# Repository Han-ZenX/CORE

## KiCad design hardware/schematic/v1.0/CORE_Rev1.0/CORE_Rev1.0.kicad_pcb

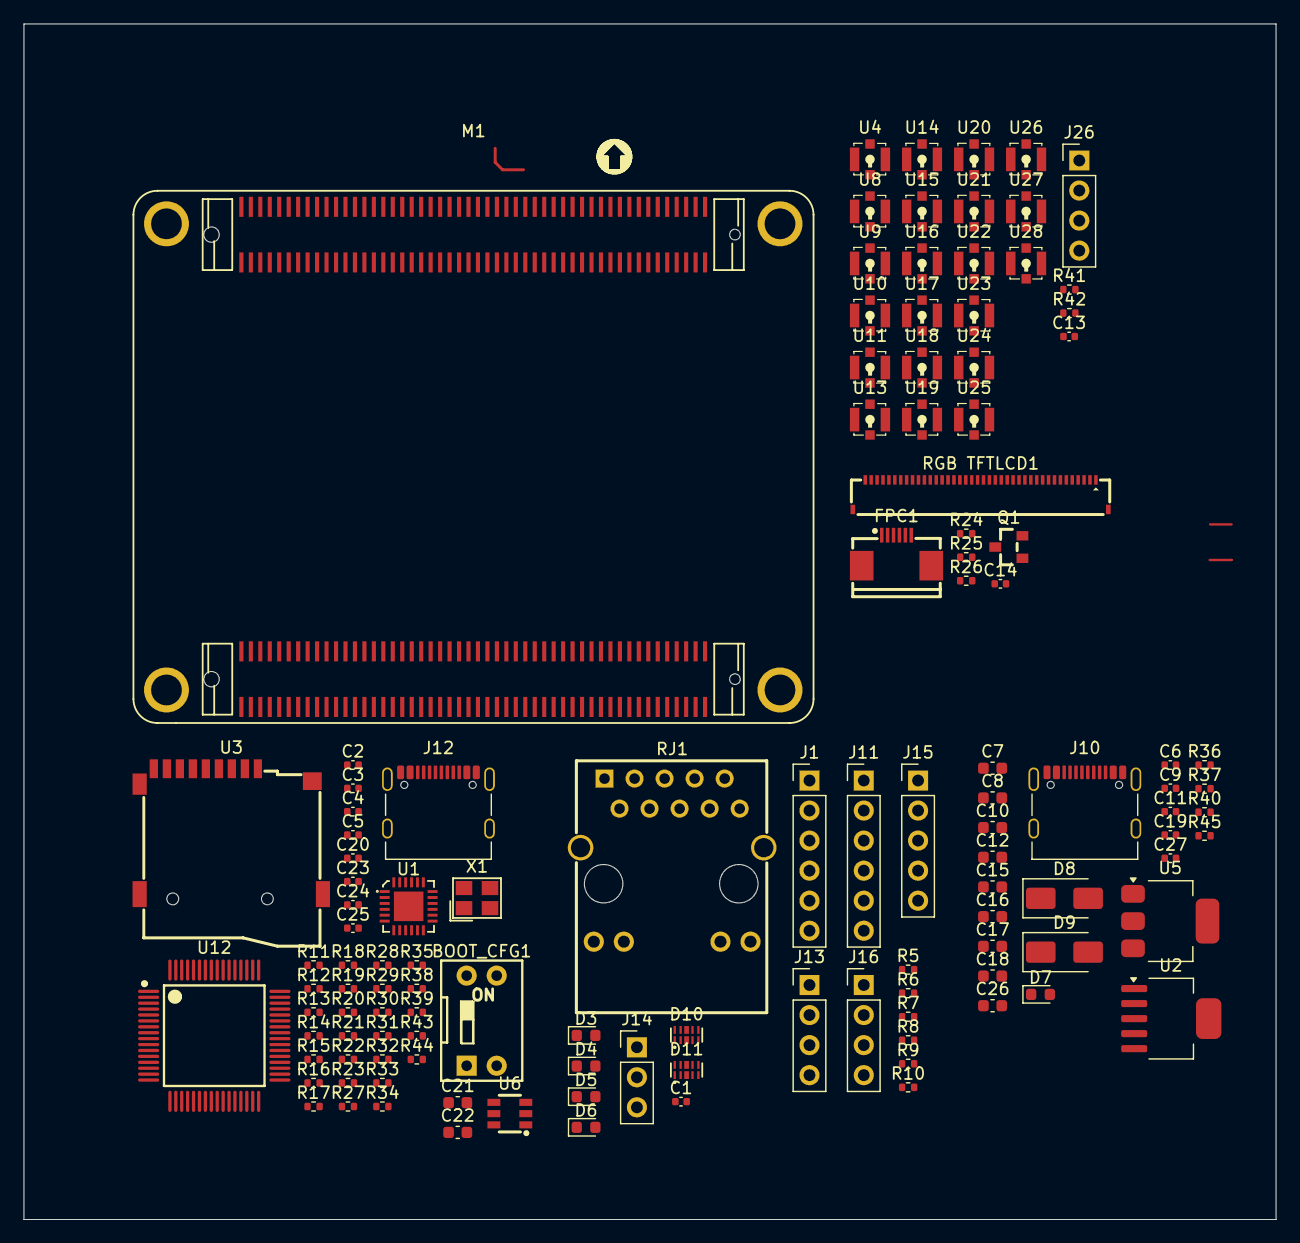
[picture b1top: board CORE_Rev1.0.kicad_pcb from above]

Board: 4 copper layers, 105.9 x 101.1 mm, 120 parts (0 on the bottom side), 163 nets.

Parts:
BOOT_CFG1: CSW-2P; CSW DIP-2P
C1, C2, C3, C5, C6, C11, C14, C19, C20, C23, C27: 100nF; C_0402_1005Metric
C4: 10uF; C_0402_1005Metric
C7, C8, C10, C12, C15, C17, C21, C22, C26: 10uF; C_0603_1608Metric
C9: 10nF; C_0402_1005Metric
C13: 1nF; C_0402_1005Metric
C16, C18: 100nF; C_0603_1608Metric
C24, C25: 30pF; C_0402_1005Metric
D3, D4, D5, D6, D7: LED; LED_0603_1608Metric
D8, D9: SS34; D_SMA
D10, D11: AZ1143-04F_R7G
FPC1: FPC-05F-6PH20
J1, J11: Conn_01x06_Socket; PinHeader_1x06_P2.54mm_Vertical
J10, J12: USB_C_Receptacle_USB2.0_16P; USB_C_Receptacle_Palconn_UTC16-G
J13, J16, J26: Conn_01x04_Socket; PinHeader_1x04_P2.54mm_Vertical
J14: Conn_01x03_Socket; PinHeader_1x03_P2.54mm_Vertical
J15: Conn_01x05_Socket; PinHeader_1x05_P2.54mm_Vertical
M1: ZYNQ7010&7020; ZYNQ7010&7020_CB
Q1: Si2302CDS-T1-GE3
R5, R6, R7, R8, R9, R10: 499R; R_0402_1005Metric
R11, R12: 20K; R_0402_1005Metric
R13, R14, R18, R24, R34: 10K; R_0402_1005Metric
R15, R19, R20, R21, R22, R23: 4.7K; R_0402_1005Metric
R16: 330; R_0402_1005Metric
R17, R40, R43, R44: 0; R_0402_1005Metric
R25, R45: 1K; R_0402_1005Metric
R26: 10; R_0402_1005Metric
R27, R28: 10R; R_0402_1005Metric
R29, R30, R31, R32: 33R; R_0402_1005Metric
R33: 2K; R_0402_1005Metric
R35: 12K/%1; R_0402_1005Metric
R36, R37, R38, R39: 5.1K; R_0402_1005Metric
R41, R42: 49.9; R_0402_1005Metric
RGB TFTLCD1: RGBLCD; LAIL-FPC-CDX01-40P0_5-GW
RJ1: HR911131A
U1: TXS02612RTWR
U2: TPS78633; SOT-223-6
U3: SD_Card; XDFP-0090-012
U4, U8, U9, U10, U11, U13, U14, U15, U16, U17, U18, U19, U20, U21, U22, U23, U24, U25, U26, U27, U28: IPEX1; JLC_IPEX-1
U5: AMS1117-1.8; SOT-223-3_TabPin2
U6: 93LC56BT-I_OT
U12: FT2232HL
X1: X322512MSB4SI

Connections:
+1.8V: C3.2, C17.1, C18.1, U1.5 (VCCA), U5.2 (VO)
+3.3V: C2.2, C4.1, C5.1, C10.2, C14.2, C15.1, C16.1, C19.2, FPC1.2, J1.3, J1.4, J11.3, J11.4, J26.1, R9.1, R10.2, R13.2, R14.2, R18.1, R19.1, R20.1, R21.1, R22.1, R23.1, R34.2, RGB TFTLCD1.1, RGB TFTLCD1.4, U1.17 (VCCB1), U1.21 (VCCB0), U2.4 (OUT), U3.4 (VDD), U5.3 (VI), U6.6 (VCC), U12.4 (VPHY), U12.9 (VPLL), U12.12 (VCORE), U12.20 (VCCIO), U12.31 (VCCIO), U12.37 (VCORE), U12.42 (VCCIO), U12.49 (VREGOUT), U12.50 (VREGIN), U12.56 (VCCIO), U12.64 (VCORE)
+5V: J1.1, J1.2, J11.1, J11.2, M1.J1_1 (1), M1.J1_2 (2), M1.J1_3 (3), M1.J1_4 (4), M1.J1_5 (5), M1.J1_6 (6), M1.J1_7 (7), M1.J1_8 (8), R40.2, R45.1, U2.2 (IN)
+5V_IN: C26.1, C27.1, D9.2 (A)
+VBUS: C20.1, C21.1, C22.1, C23.1, J12.A4 (VBUS), J12.A9 (VBUS), J12.B4 (VBUS), J12.B9 (VBUS)
+VBUS_5V: C6.1, C7.1, C11.1, C12.1, D8.2 (A), J10.A4 (VBUS), J10.A9 (VBUS), J10.B4 (VBUS), J10.B9 (VBUS)
/Comm_Periph/IO0: J13.1, M1.J2_41 (41)
/Comm_Periph/IO1: J13.2, M1.J2_43 (43)
/Comm_Periph/IO2: J13.3, M1.J2_45 (45)
/Comm_Periph/IO3: J13.4, M1.J2_47 (47)
/Comm_Periph/IO4: J16.1, M1.J2_49 (49)
/Comm_Periph/IO5: J16.2, M1.J2_51 (51)
/Comm_Periph/IO6: J16.3, M1.J2_53 (53)
/Comm_Periph/IO7: J16.4, M1.J2_57 (57)
/Comm_Periph/PHY1_AD0/LED0: M1.J2_1 (1), RJ1.12 (G-)
/Comm_Periph/PHY1_AD1/LED1: M1.J2_2 (2), RJ1.13 (Y-)
/Comm_Periph/PHY1_MDI0_N: D10.2 (Line-2), M1.J2_5 (5)
/Comm_Periph/PHY1_MDI0_P: D10.1 (Line-1), M1.J2_3 (3)
/Comm_Periph/PHY1_MDI1_N: D10.5 (Line-4), M1.J2_9 (9)
/Comm_Periph/PHY1_MDI1_P: D10.4 (Line-3), M1.J2_7 (7)
/Comm_Periph/PHY1_MDI2_N: D11.2 (Line-2), M1.J2_6 (6)
/Comm_Periph/PHY1_MDI2_P: D11.1 (Line-1), M1.J2_4 (4)
/Comm_Periph/PHY1_MDI3_N: D11.5 (Line-4), M1.J2_10 (10)
/Comm_Periph/PHY1_MDI3_P: D11.4 (Line-3), M1.J2_8 (8)
/Comm_Periph/PL_LED0: M1.J2_44 (44), R5.1
/Comm_Periph/PL_LED1: M1.J2_55 (55), R6.1
/Comm_Periph/PS_I2C_SCL: J14.2, M1.J2_65 (65)
/Comm_Periph/PS_I2C_SDA: J14.1, M1.J2_70 (70)
/Comm_Periph/PS_LED0: M1.J2_92 (92), R7.1
/Comm_Periph/PS_LED1: M1.J2_95 (95), R8.1
/Comm_Periph/PS_SPI1_MISO: J15.2, M1.J2_94 (94)
/Comm_Periph/PS_SPI1_MOSI: J15.1, M1.J2_91 (91)
/Comm_Periph/PS_SPI1_SCLK: J15.3, M1.J2_90 (90)
/Comm_Periph/PS_SPI1_SS0: J15.4, M1.J2_93 (93)
/Display/CTP_INT: FPC1.4, M1.J1_53 (53)
/Display/CTP_RST: FPC1.1, M1.J1_51 (51)
/Display/CTP_SCL: FPC1.6, M1.J1_57 (57)
/Display/CTP_SDA: FPC1.5, M1.J1_55 (55)
/Display/LCD_B0: M1.J1_44 (44), RGB TFTLCD1.21
/Display/LCD_B1: M1.J1_46 (46), RGB TFTLCD1.22
/Display/LCD_B2: M1.J1_43 (43), RGB TFTLCD1.23
/Display/LCD_B3: M1.J1_45 (45), RGB TFTLCD1.24
/Display/LCD_B4: M1.J1_48 (48), RGB TFTLCD1.25
/Display/LCD_B5: M1.J1_50 (50), RGB TFTLCD1.26
/Display/LCD_B6: M1.J1_47 (47), RGB TFTLCD1.27
/Display/LCD_B7: M1.J1_49 (49), RGB TFTLCD1.28
/Display/LCD_BLK: M1.J1_24 (24), R25.1
/Display/LCD_CLK: M1.J1_54 (54), RGB TFTLCD1.30
/Display/LCD_DE: M1.J1_62 (62), RGB TFTLCD1.34
/Display/LCD_DISP: M1.J1_56 (56), RGB TFTLCD1.31
/Display/LCD_G0: M1.J1_33 (33), RGB TFTLCD1.13
/Display/LCD_G1: M1.J1_35 (35), RGB TFTLCD1.14
/Display/LCD_G2: M1.J1_36 (36), RGB TFTLCD1.15
/Display/LCD_G3: M1.J1_38 (38), RGB TFTLCD1.16
/Display/LCD_G4: M1.J1_37 (37), RGB TFTLCD1.17
/Display/LCD_G5: M1.J1_39 (39), RGB TFTLCD1.18
/Display/LCD_G6: M1.J1_40 (40), RGB TFTLCD1.19
/Display/LCD_G7: M1.J1_42 (42), RGB TFTLCD1.20
/Display/LCD_HSYNC: M1.J1_58 (58), RGB TFTLCD1.32
/Display/LCD_R0: M1.J1_26 (26), RGB TFTLCD1.5
/Display/LCD_R1: M1.J1_28 (28), RGB TFTLCD1.6
/Display/LCD_R2: M1.J1_25 (25), RGB TFTLCD1.7
/Display/LCD_R3: M1.J1_27 (27), RGB TFTLCD1.8
/Display/LCD_R4: M1.J1_30 (30), RGB TFTLCD1.9
/Display/LCD_R5: M1.J1_32 (32), RGB TFTLCD1.10
/Display/LCD_R6: M1.J1_29 (29), RGB TFTLCD1.11
/Display/LCD_R7: M1.J1_31 (31), RGB TFTLCD1.12
/Display/LCD_VSYNC: M1.J1_60 (60), RGB TFTLCD1.33
/Display/LEDK: R26.2, RGB TFTLCD1.2
/Signal/CLK1_FS_N: M1.J1_18 (18), U11.4 (SIG)
/Signal/CLK1_FS_P: M1.J1_16 (16), U10.4 (SIG)
/Signal/CLK1_FX_N: M1.J2_18 (18), U9.4 (SIG)
/Signal/CLK1_FX_P: M1.J2_20 (20), U8.4 (SIG)
/Signal/CLK2_FS_N: M1.J1_83 (83), U16.4 (SIG)
/Signal/CLK2_FS_P: M1.J1_81 (81), U15.4 (SIG)
/Signal/CLK2_FX_N: M1.J2_26 (26), U18.4 (SIG)
/Signal/CLK2_FX_P: M1.J2_28 (28), U17.4 (SIG)
/Signal/CLK3_FX_N: M1.J2_38 (38), U20.4 (SIG)
/Signal/CLK3_FX_P: M1.J2_40 (40), U19.4 (SIG)
/Signal/CLK4_FX_N: M1.J2_50 (50), U22.4 (SIG)
/Signal/CLK4_FX_P: M1.J2_52 (52), U21.4 (SIG)
/Signal/CLK5_FX_N: M1.J2_58 (58), U24.4 (SIG)
/Signal/CLK5_FX_P: M1.J2_60 (60), U23.4 (SIG)
/Signal/CLK6_FX_N: M1.J2_19 (19), U26.4 (SIG)
/Signal/CLK6_FX_P: M1.J2_17 (17), U25.4 (SIG)
/Signal/CLK7_FX_N: M1.J2_27 (27), U28.4 (SIG)
/Signal/CLK7_FX_P: M1.J2_25 (25), U27.4 (SIG)
/Signal/CLK_10M: M1.J1_77 (77), U4.4 (SIG)
/Signal/CLK_FX8_N: M1.J2_35 (35), U14.4 (SIG)
/Signal/CLK_FX8_P: M1.J2_33 (33), U13.4 (SIG)
/Signal/XADC_VN: M1.J2_85 (85), R42.1
/Signal/XADC_VP: M1.J2_83 (83), R41.2
/Storage/BOOT_MODE0: M1.J2_81 (81), R11.2
/Storage/BOOT_MODE1: M1.J2_79 (79), R12.2
/Storage/FPGA_TCK: M1.J2_99 (99), R29.2
/Storage/FPGA_TDI: M1.J2_98 (98), R30.2
/Storage/FPGA_TDO: M1.J2_97 (97), R31.2
/Storage/FPGA_TMS: M1.J2_100 (100), R32.2
/Storage/PS_RXD: M1.J2_89 (89), R43.2
/Storage/PS_TXD: M1.J2_87 (87), R44.1
/Storage/SD_CD: M1.J2_96 (96), R17.1
/Storage/SD_CLK: M1.J2_80 (80), U1.9 (CLKA)
/Storage/SD_CMD: M1.J2_78 (78), U1.4 (CMDA)
/Storage/SD_D0: M1.J2_82 (82), U1.6 (DAT0A)
/Storage/SD_D1: M1.J2_84 (84), U1.7 (DAT1A)
/Storage/SD_D2: M1.J2_86 (86), U1.1 (DAT2A)
/Storage/SD_D3: M1.J2_88 (88), U1.3 (DAT3A)
GND: BOOT_CFG1.1, BOOT_CFG1.2, C1.1, C2.1, C3.1, C4.2, C5.2, C6.2, C7.2, C8.1, C9.1, C10.1, C11.2, C12.2, C14.1, C15.2, C16.2, C17.2, C18.2, C19.1, C20.2, C21.2, C22.2, C23.2, C24.1, C25.1, C26.2, C27.2, D3.1 (K), D4.1 (K), D5.1 (K), D6.1 (K), D7.1 (K), D10.3 (GND), D10.8 (GND), D11.3 (GND), D11.8 (GND), FPC1.3, FPC1.7, FPC1.8, J1.5, J1.6, J10.A1 (GND), J10.A12 (GND), J10.B1 (GND), J10.B12 (GND), J10.SH (SHIELD), J11.5, J11.6, J12.A1 (GND), J12.A12 (GND), J12.B1 (GND), J12.B12 (GND), J12.SH (SHIELD), J14.3, J15.5, J26.4, M1.J1_19 (19), M1.J1_34 (34), M1.J1_41 (41), M1.J1_52 (52), M1.J1_59 (59), M1.J1_70 (70), M1.J1_93 (93), M1.J1_94 (94), M1.J1_95 (95), M1.J1_96 (96), M1.J1_97 (97), M1.J1_98 (98), M1.J1_99 (99), M1.J1_100 (100), M1.J2_11 (11), M1.J2_12 (12), M1.J2_62 (62), M1.J2_63 (63), M1.J2_76 (76), M1.J2_77 (77), Q1.2 (S), R15.2, R24.2, R35.1, R36.2, R37.1, R38.2, R39.1, RGB TFTLCD1.3, RGB TFTLCD1.29, RGB TFTLCD1.36, RJ1.15 (EH), RJ1.16 (EH), U1.2 (GND1), U1.11 (GND2), U1.25 (EPAD), U2.3 (GND), U2.6 (TAB), U3.6 (VSS), U3.10 (GND), U4.1 (GND), U4.2 (GND), U4.3 (GND), U5.1 (GND), U6.2 (VSS), U8.1 (GND), U8.2 (GND), U8.3 (GND), U9.1 (GND), U9.2 (GND), U9.3 (GND), U10.1 (GND), U10.2 (GND), U10.3 (GND), U11.1 (GND), U11.2 (GND), U11.3 (GND), U12.1 (GND), U12.5 (GND), U12.10 (AGND), U12.11 (GND), U12.13 (TEST), U12.15 (GND), U12.25 (GND), U12.35 (GND), U12.47 (GND), U12.51 (GND), U13.1 (GND), U13.2 (GND), U13.3 (GND), U14.1 (GND), U14.2 (GND), U14.3 (GND), U15.1 (GND), U15.2 (GND), U15.3 (GND), U16.1 (GND), U16.2 (GND), U16.3 (GND), U17.1 (GND), U17.2 (GND), U17.3 (GND), U18.1 (GND), U18.2 (GND), U18.3 (GND), U19.1 (GND), U19.2 (GND), U19.3 (GND), U20.1 (GND), U20.2 (GND), U20.3 (GND), U21.1 (GND), U21.2 (GND), U21.3 (GND), U22.1 (GND), U22.2 (GND), U22.3 (GND), U23.1 (GND), U23.2 (GND), U23.3 (GND), U24.1 (GND), U24.2 (GND), U24.3 (GND), U25.1 (GND), U25.2 (GND), U25.3 (GND), U26.1 (GND), U26.2 (GND), U26.3 (GND), U27.1 (GND), U27.2 (GND), U27.3 (GND), U28.1 (GND), U28.2 (GND), U28.3 (GND), X1.2 (GND), X1.4 (GND)
unnamed: BOOT_CFG1.3, R12.1, R14.1
unnamed: BOOT_CFG1.4, R11.1, R13.1
unnamed: C1.2, RJ1.P5, RJ1.P6
unnamed: D3.2 (A), R5.2
unnamed: D4.2 (A), R6.2
unnamed: D5.2 (A), R7.2
unnamed: D6.2 (A), R8.2
unnamed: D7.2 (A), R45.2
unnamed: D8.1 (K), D9.1 (K)
unnamed: D10.6 (NC), RJ1.P4
unnamed: D10.7 (NC), RJ1.P3
unnamed: D10.9 (NC), RJ1.P2
unnamed: D10.10 (NC), RJ1.P1
unnamed: D11.6 (NC), RJ1.P10
unnamed: D11.7 (NC), RJ1.P9
unnamed: D11.9 (NC), RJ1.P8
unnamed: D11.10 (NC), RJ1.P7
unnamed: J10.A5 (CC1), R36.1
unnamed: J10.B5 (CC2), R37.2
unnamed: J12.A5 (CC1), R38.1
unnamed: J12.B5 (CC2), R39.2
unnamed: J12.A6 (D+), J12.B6 (D+), R28.1
unnamed: J12.A7 (D-), J12.B7 (D-), R27.1
unnamed: C13.1, J26.2, R41.1
unnamed: C13.2, J26.3, R42.2
unnamed: Q1.3 (D), R26.1
unnamed: Q1.1 (G), R24.1, R25.2
unnamed: R16.1, R17.2, R18.2
unnamed: R9.2, RJ1.11 (G+)
unnamed: R10.1, RJ1.14 (Y+)
unnamed: U1.19 (CLKB0), U3.5 (CLK/SLCK)
unnamed: R21.2, U1.20 (CMDB0), U3.3 (CMD/SDI)
unnamed: R20.2, U1.18 (DAT0B0), U3.7 (DAT0/SDO)
unnamed: R19.2, U1.16 (DAT1B0), U3.8 (DAT1)
unnamed: R23.2, U1.23 (DAT2B0), U3.1 (DAT2)
unnamed: R22.2, U1.22 (DAT3B0), U3.2 (CD/DAT3/CS)
unnamed: R15.1, U1.24 (SEL)
unnamed: C8.2, R40.1, U2.1 (EN)
unnamed: C9.2, U2.5 (NR/FB)
unnamed: R16.2, U3.9 (CD/SW)
unnamed: R33.2, R34.1, U6.1 (DO)
unnamed: R29.1, U12.16 (ADBUS0)
unnamed: R30.1, U12.17 (ADBUS1)
unnamed: R31.1, U12.18 (ADBUS2)
unnamed: R32.1, U12.19 (ADBUS3)
unnamed: R43.1, U12.38 (BDBUS0)
unnamed: R44.2, U12.39 (BDBUS1)
unnamed: R27.2, U12.7 (DM)
unnamed: R28.2, U12.8 (DP)
unnamed: U6.4 (CLK), U12.62 (EECLK)
unnamed: U6.5 (CS), U12.63 (EECS)
unnamed: R33.1, U6.3 (DI), U12.61 (EEDATA)
unnamed: C24.2, U12.2 (OSCI), X1.1
unnamed: C25.2, U12.3 (OSCO), X1.3
unnamed: R35.2, U12.6 (REF)
